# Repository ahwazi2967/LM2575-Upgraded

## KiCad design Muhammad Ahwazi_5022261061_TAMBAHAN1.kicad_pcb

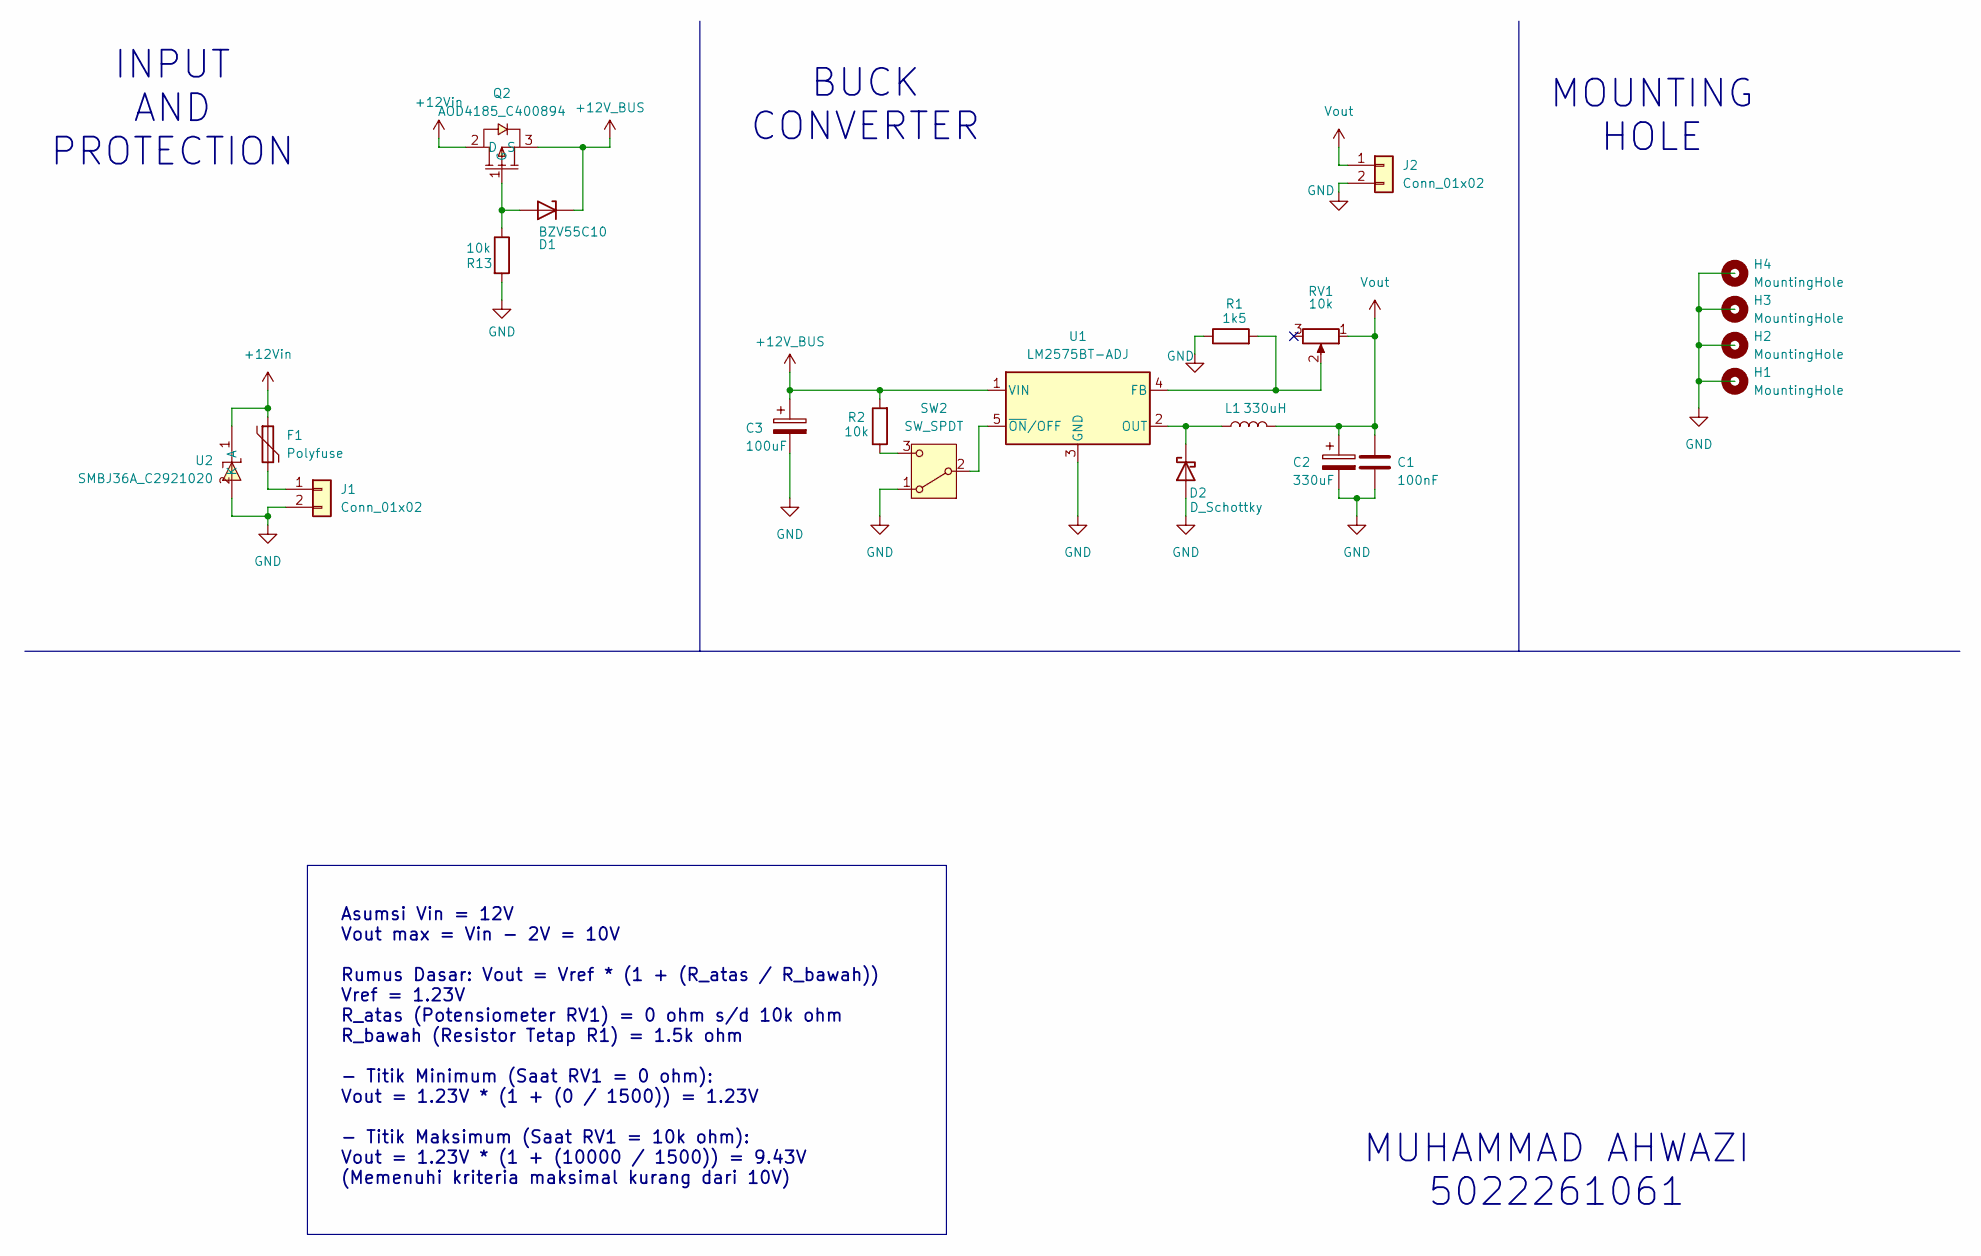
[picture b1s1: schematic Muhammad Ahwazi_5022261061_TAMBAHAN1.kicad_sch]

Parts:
C1: 100nF; C_0805_2012Metric
C2: 330uF; CP_Elec_8x10
C3: 100uF; CP_Elec_8x10
D1: BZV55C10; D_MiniMELF
D2: D_Schottky; D_SMA
F1: Polyfuse; Fuse_2920_7451Metric
H1, H2, H3, H4: MountingHole; MountingHole_2.1mm
J1, J2: Conn_01x02; TerminalBlock_Phoenix_MKDS-1,5-2-5.08_1x02_P5.08mm_Horizont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
L1: 330uH; L_12x12mm_H6mm
Q2: AOD4185_C400894; TO-252-3_L6.6-W6.1-P4.57-LS9.9-BR-CW; MPN AOD4185; LCSC Part C400894
R1: 1k5; R_0805_2012Metric
R2, R13: 10k; R_0805_2012Metric
RV1: 10k; Potentiometer_Bourns_3296W_Vertical
SW2: SW_SPDT; SW_Slide_SPDT_Straight_CK_OS102011MS2Q
U1: LM2575BT-ADJ; TO-220-5_Vertical
U2: SMBJ36A_C2921020; SMB_L4.5-W3.7-LS5.4-RD; MPN SMBJ36A; LCSC Part C2921020

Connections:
+12V_BUS: C3.1, D1.1 (K), Q2.3 (S), R2.2, U1.1 (VIN)
+12Vin: F1.1, Q2.2 (D), U2.1 (K)
GND: C1.2, C2.2, C3.2, D2.2 (A), J1.2, J2.2, R1.1, R13.2, SW2.1 (A), U1.3 (GND), U2.2 (A)
unnamed: D1.2 (A), Q2.1 (G), R13.1
unnamed: D2.1 (K), L1.1, U1.2 (OUT)
unnamed: F1.2, J1.1
unnamed: SW2.2 (B), U1.5 (~ON/OFF)
unnamed: R2.1, SW2.3 (C)
unnamed: R1.2, RV1.2, U1.4 (FB)
Vout: C1.1, C2.1, J2.1, L1.2, RV1.1

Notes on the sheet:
MUHAMMAD AHWAZI 5022261061
INPUT AND PROTECTION
MOUNTING HOLE
BUCK CONVERTER
Asumsi Vin = 12V Vout max = Vin - 2V = 10V Rumus Dasar: Vout = Vref * (1 + (R_atas / R_bawah)) Vref = 1.23V R_atas (Potensiometer RV1) = 0 ohm s/d 10k ohm R_bawah (Resistor Tetap R1) = 1.5k ohm - Titik Minimum (Saat RV1 = 0 ohm): Vout = 1.23V * (1 + (0 / 1500)) = 1.23V - Titik Maksimum (Saat RV1 = 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

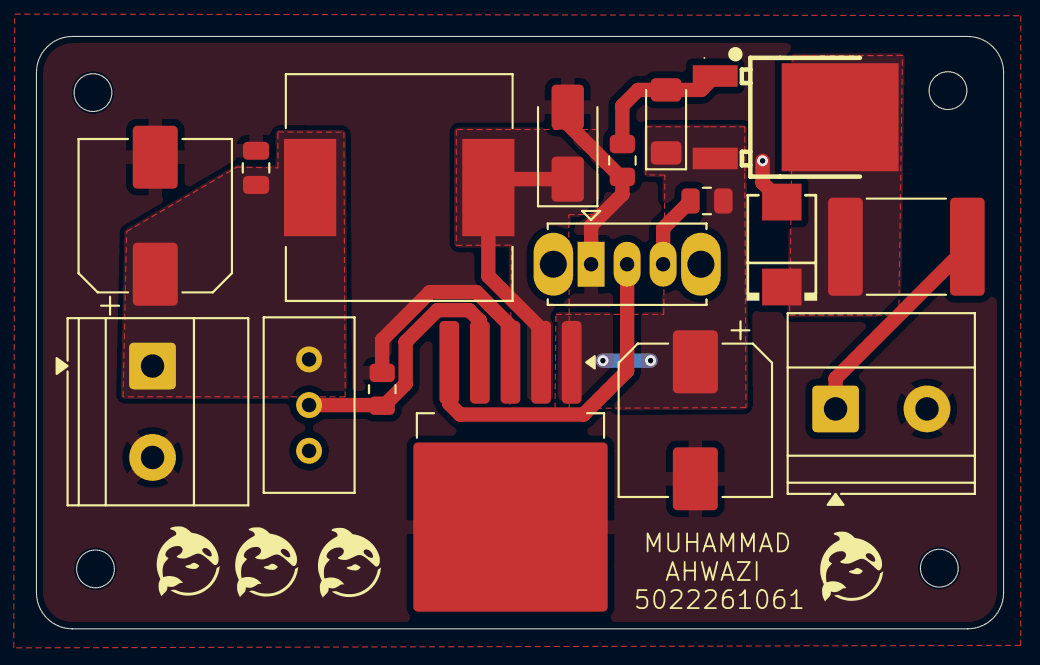
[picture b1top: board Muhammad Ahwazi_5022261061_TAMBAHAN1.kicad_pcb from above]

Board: 2 copper layers, 53.7 x 32.9 mm, 21 parts (0 on the bottom side), 10 nets.
